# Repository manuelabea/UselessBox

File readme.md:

Ziel von diesem Projekt ist es, eine sogenannte "Useless Box" zu erstellen, aber nicht nur eine primitive, sondern 
eine, die "Charakter" hat. Die Box soll, je nach Aktion des Nutzers reagieren, und nach und nach genervter werden.

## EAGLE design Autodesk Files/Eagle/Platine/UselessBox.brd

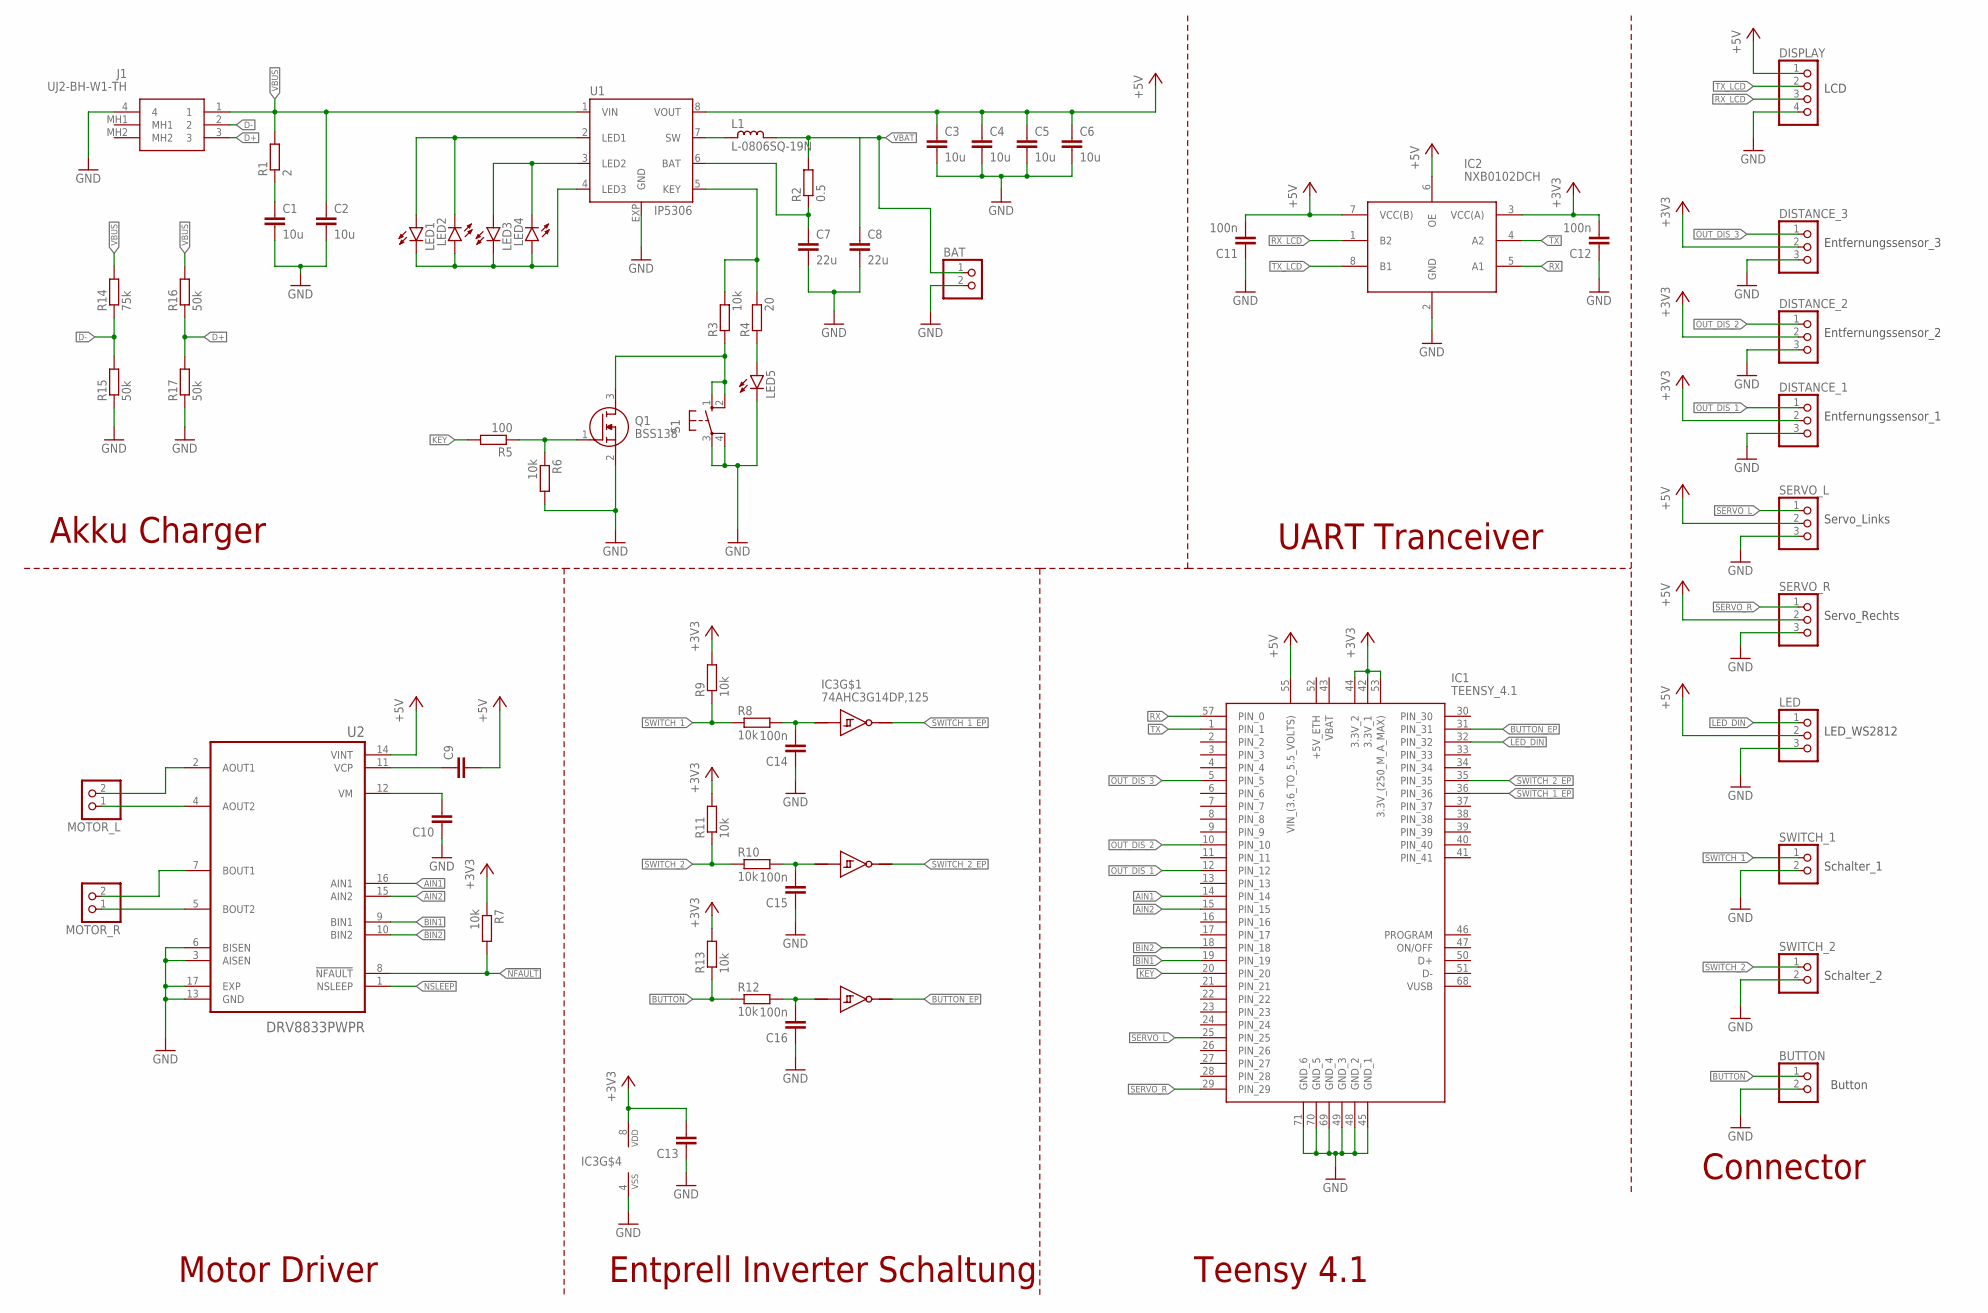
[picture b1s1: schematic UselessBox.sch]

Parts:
BAT: PINHD-1X2; 1X02
BUTTON: PINHD-1X2; 1X02
C1, C2, C3, C4, C5, C6: 10u; C1206
C7, C8: 22u; C1206
C9, C10, C13: C-EUC0805; C0805
C11, C12, C14, C15, C16: 100n; C0805
DISPLAY: PINHD-1X4; 1X04
DISTANCE_1, DISTANCE_2, DISTANCE_3: PINHD-1X3; 1X03
IC1: TEENSY_4.1; TEENSY41
IC2: NXB0102DCH; SOP50P310X100-8N
IC3: 74AHC3G14DP,125; SOP65P400X110-8N
J1: UJ2-BH-W1-TH; UJ2BHW1TH
L1: L-0806SQ-19N; 0806SQ-19N
LED: PINHD-1X3; 1X03
LED1, LED2, LED3, LED4, LED5: LEDCHIPLED_0805; CHIPLED_0805
MOTOR_L: PINHD-1X2; 1X02
MOTOR_R: PINHD-1X2; 1X02
Q1: BSS138; SOT95P240X120-3N
R1: 2; R0805
R2: 0.5; R0805
R3, R6, R7, R8, R9, R10, R11, R12, R13: 10k; R0805
R4: 20; R0805
R5: 100; R0805
R14: 75k; R0805
R15, R16, R17: 50k; R0805
S1: 10-XX; B3F-10XX
SERVO_L: PINHD-1X3; 1X03
SERVO_R: PINHD-1X3; 1X03
SWITCH_1, SWITCH_2: PINHD-1X2; 1X02
U1: IP5306; SOP8-P
U2: DRV8833PWPR; IC_DRV8833PWPR

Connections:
!NFAULT: R7.2, U2.8 (!NFAULT)
+3V3: C12.2, C13.2, DISTANCE_1.2, DISTANCE_2.2, DISTANCE_3.2, IC1.42 (3.3V_1), IC1.44 (3.3V_2), IC1.53 (3.3V_(250_M_A_MAX)), IC2.3 (VCC(A)), IC3.8 (VDD), R7.1, R9.2, R11.2, R13.2
+5V: C3.1, C4.1, C5.1, C6.1, C9.2, C11.2, DISPLAY.1, IC1.55 (VIN_(3.6_TO_5.5_VOLTS)), IC2.6 (OE), IC2.7 (VCC(B)), LED.2, SERVO_L.2, SERVO_R.2, U1.8 (VOUT), U2.14 (VINT)
AIN1: IC1.14 (PIN_14), U2.16 (AIN1)
AIN2: IC1.15 (PIN_15), U2.15 (AIN2)
BIN1: IC1.19 (PIN_19), U2.9 (BIN1)
BIN2: IC1.18 (PIN_18), U2.10 (BIN2)
BUTTON: BUTTON.1, R12.1, R13.1
BUTTON_EP: IC1.31 (PIN_31), IC3.2 (Y)
D+: J1.3, R16.1, R17.2
D-: J1.2, R14.1, R15.2
GND: BAT.2, BUTTON.2, C1.2, C2.2, C3.2, C4.2, C5.2, C6.2, C7.2, C8.2, C10.1, C11.1, C12.1, C13.1, C14.1, C15.1, C16.1, DISPLAY.4, DISTANCE_1.3, DISTANCE_2.3, DISTANCE_3.3, IC1.45 (GND_1), IC1.48 (GND_2), IC1.49 (GND_3), IC1.69 (GND_4), IC1.70 (GND_5), IC1.71 (GND_6), IC2.2 (GND), IC3.4 (VSS), J1.4, LED.3, LED5.C, Q1.2 (S), R6.2, R15.1, R17.1, S1.3, S1.4 (P1), SERVO_L.3, SERVO_R.3, SWITCH_1.2, SWITCH_2.2, U1.EXP (GND), U2.3 (AISEN), U2.6 (BISEN), U2.13 (GND), U2.17 (EXP)
KEY: IC1.20 (PIN_20), R5.2
LED_DIN: IC1.32 (PIN_32), LED.1
unnamed: LED1.A, LED2.C, U1.2 (LED1)
unnamed: LED3.A, LED4.C, U1.3 (LED2)
unnamed: LED1.C, LED2.A, LED3.C, LED4.A, U1.4 (LED3)
unnamed: C1.1, R1.1
unnamed: LED5.A, R4.1
unnamed: C7.1, R2.1, U1.6 (BAT)
unnamed: R3.2, R4.2, U1.5 (KEY)
unnamed: Q1.1 (G), R5.1, R6.1
unnamed: Q1.3 (D), R3.1, S1.1 (S), S1.2 (S1)
unnamed: L1.1, U1.7 (SW)
unnamed: MOTOR_L.1, U2.4 (AOUT2)
unnamed: MOTOR_L.2, U2.2 (AOUT1)
unnamed: MOTOR_R.1, U2.5 (BOUT2)
unnamed: MOTOR_R.2, U2.7 (BOUT1)
unnamed: C9.1, U2.11 (VCP)
unnamed: C10.2, U2.12 (VM)
unnamed: C15.2, IC3.3 (A), R10.2
unnamed: C14.2, IC3.1 (A), R8.2
unnamed: C16.2, IC3.6 (A), R12.2
NSLEEP: U2.1 (NSLEEP)
OUT_DIS_1: DISTANCE_1.1, IC1.12 (PIN_12)
OUT_DIS_2: DISTANCE_2.1, IC1.10 (PIN_10)
OUT_DIS_3: DISTANCE_3.1, IC1.5 (PIN_5)
RX: IC1.57 (PIN_0), IC2.5 (A1)
RX_LCD: DISPLAY.3, IC2.1 (B2)
SERVO_L: IC1.25 (PIN_25), SERVO_L.1
SERVO_R: IC1.29 (PIN_29), SERVO_R.1
SWITCH_1: R8.1, R9.1, SWITCH_1.1
SWITCH_1_EP: IC1.36 (PIN_36), IC3.7 (Y)
SWITCH_2: R10.1, R11.1, SWITCH_2.1
SWITCH_2_EP: IC1.35 (PIN_35), IC3.5 (Y)
TX: IC1.1 (PIN_1), IC2.4 (A2)
TX_LCD: DISPLAY.2, IC2.8 (B1)
VBAT: BAT.1, C8.1, L1.2, R2.2
VBUS: C2.1, J1.1, R1.2, R14.2, R16.2, U1.1 (VIN)

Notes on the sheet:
Entfernungssensor_1
Servo_Links
Servo_Rechts
LED_WS2812
Entfernungssensor_2
LCD
Schalter_1
Schalter_2
Button
Akku Charger
UART Tranceiver
Connector
Teensy 4.1
Entprell Inverter Schaltung
Motor Driver
Entfernungssensor_3

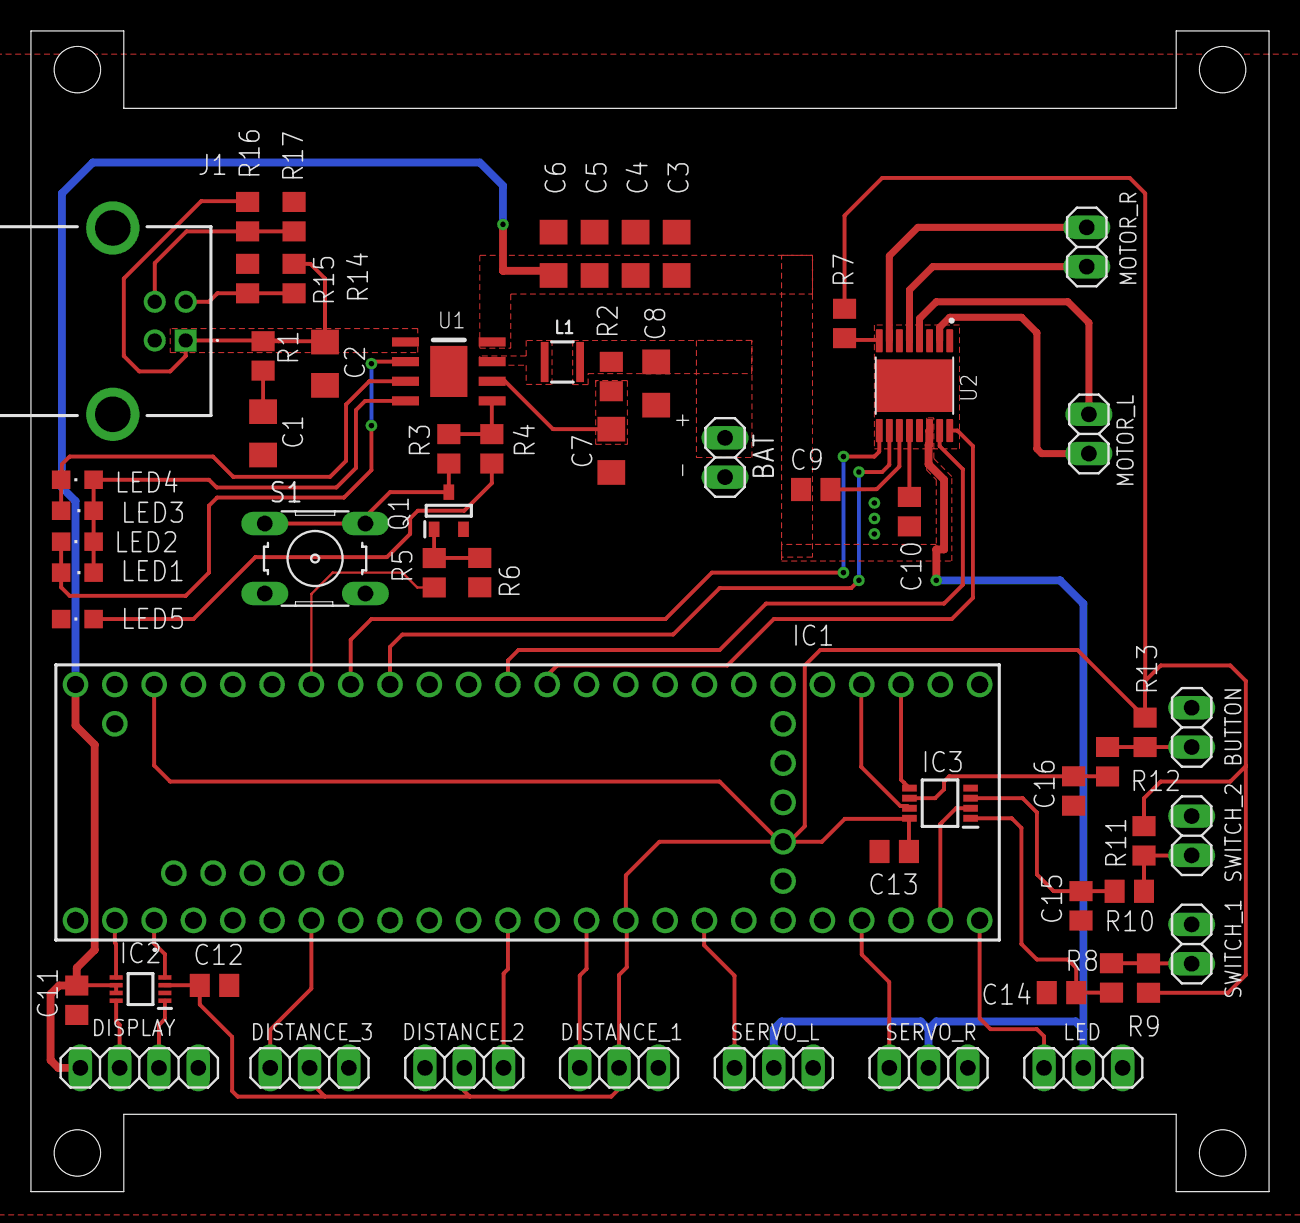
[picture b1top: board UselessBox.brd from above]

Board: 2 copper layers, 80.0 x 75.0 mm, 60 parts (0 on the bottom side), 48 nets.

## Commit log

2021-11-04 erster Testcode Display
2021-12-20 Added e-ink libraries and a bit of project structure
2021-12-24 Erste Testcodes und etwas Doku zu den Bauteilen
2021-12-24 Problem mit Kippschalter/Toggle Switch/Taster gelöst
2021-12-24 Kombination Taster und Toggle Switch
2021-12-25 Servo mit Interrupt
2021-12-26 Servo unvorhergesehenes Verhalten korrigiert
2021-12-26 aktuellster Stand
2021-12-26 nach 2 Stunden geschafft zu iterieren
2022-09-26 Create InfosVomFlo
2022-10-10 Dokumentation
2022-10-10 question
2022-10-11 - Dokumentation fortgeführt - Servo objektorientiert angesteuert
2022-10-11 - Dokumentation um heutigen Fortschritt ergänzt
2022-10-20 Dokumentation ergänzt
2022-10-21 FastLED Code
2022-10-22 - Interrupt works for a button - Created an interrupt that counts actions, but he interrupts twice when the switch is toggled - With Moritz help created the framework for a correctly working interrup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
2022-10-23 Den Ansatz von Moritz probiert, klappt... nur iteriert er jedes Mal, wenn der Schalter umgelegt wird
2022-10-25 Finally the toggle works in one direction!!
2022-11-15 ...toggle klappt wieder nicht
2022-11-16 Display .hmi Files added
2022-11-22 Doku ergänzt
2023-01-13 Eagle
2023-01-19 .
    :
2023-01-19 Create deleteLater
